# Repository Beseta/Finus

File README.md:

# Finus

Digital guitar tuner based on an Arduino Uno board.

## Hardware

The schematic was based on Anthony Kelly's design which can be found [here](http://www.akellyirl.com/arduino-guitar-tuner/). Some values were tweaked to accomodate what I had lying around in my office.

## Software

The basic code for the DSP was based on Amanda Ghassaei's [Arduino Frequency Detection](https://www.instructables.com/Arduino-Frequency-Detection/). I modified several lines of code to consider the differences in our hardware implementation.

## Pictures

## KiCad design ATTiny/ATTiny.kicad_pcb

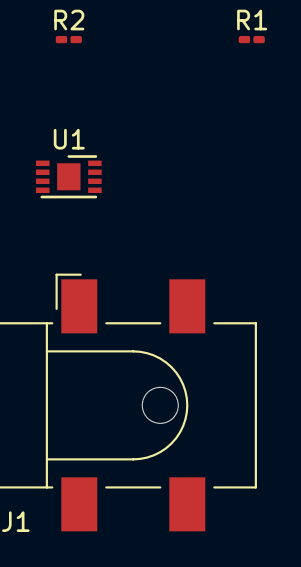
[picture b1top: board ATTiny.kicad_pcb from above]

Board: 2 copper layers, 4 parts (0 on the bottom side), 3 nets, no tracks yet.

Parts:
J1: DC Jack; BarrelJack_CLIFF_FC681465S_SMT_Horizontal
R1: 1.2K; R_0201_0603Metric_Pad0.64x0.40mm_HandSolder
R2: 1.5K; R_0201_0603Metric_Pad0.64x0.40mm_HandSolder
U1: ATtiny102-M; DFN-8-1EP_3x2mm_P0.5mm_EP1.3x1.5mm

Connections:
GND: J1.1, R2.2, U1.8 (GND)
unnamed: J1.2, R1.1
VCC: R1.2, R2.1, U1.1 (VCC)

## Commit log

2022-12-08 first commit, first version
2022-12-09 add KiCad files
2022-12-09 basic string parsing
2022-12-14 finished arduino version
2023-04-17 add pics
